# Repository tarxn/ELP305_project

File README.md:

# BIG BLACK co.
BIG BLACK Chargers & BIG BLACK Cables

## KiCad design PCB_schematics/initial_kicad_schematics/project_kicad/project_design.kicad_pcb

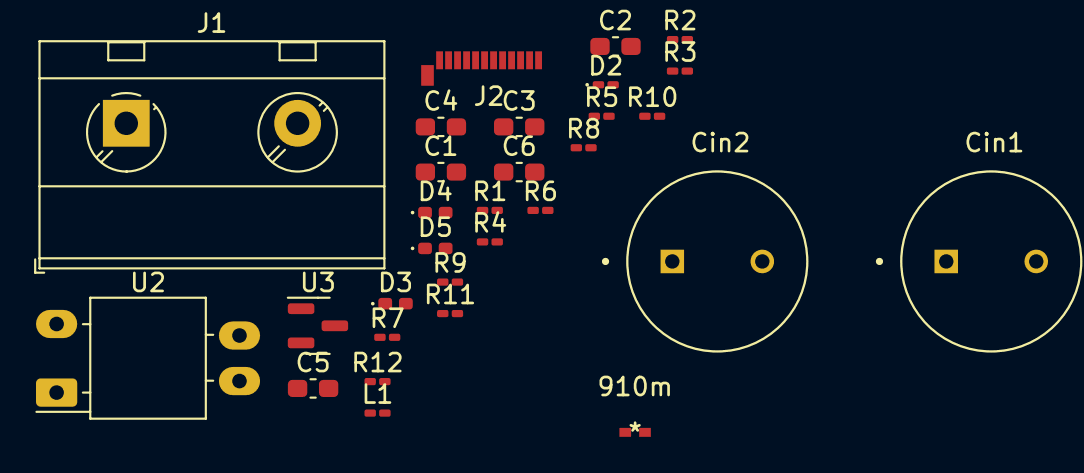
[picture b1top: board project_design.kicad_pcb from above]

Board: 2 copper layers, 30 parts (0 on the bottom side), 15 nets, no tracks yet.

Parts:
C1, C2: 22uF; C_0603_1608Metric_Pad1.08x0.95mm_HandSolder
C3: 4.7uF; C_0603_1608Metric_Pad1.08x0.95mm_HandSolder
C4: 100nF; C_0603_1608Metric_Pad1.08x0.95mm_HandSolder
C5: 882.393pF; C_0603_1608Metric_Pad1.08x0.95mm_HandSolder
C6: 1.2mF; C_0603_1608Metric_Pad1.08x0.95mm_HandSolder
Cin1, Cin2: 22uF; 400PK22MEFC12.5X20
D2: D_Zener; D_0201_0603Metric_Pad0.64x0.40mm_HandSolder
D3, D4, D5: D; D_0402_1005Metric_Pad0.77x0.64mm_HandSolder
J1: Screw_Terminal_01x02; TerminalBlock_MetzConnect_Type703_RT10N02HGLU_1x02_P9.52mm_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
J2: USB_C_Receptacle_PowerOnly_6P; USB_C_Plug_Molex_105444
L1: 470uH; L_0201_0603Metric_Pad0.64x0.40mm_HandSolder
R1: R; R_0201_0603Metric_Pad0.64x0.40mm_HandSolder
R2: 910m; R_0201_0603Metric_Pad0.64x0.40mm_HandSolder
R3: 2.21k; R_0201_0603Metric_Pad0.64x0.40mm_HandSolder
R4: 18.7k; R_0201_0603Metric_Pad0.64x0.40mm_HandSolder
R5: 205k; R_0201_0603Metric_Pad0.64x0.40mm_HandSolder
R6: 113k; R_0201_0603Metric_Pad0.64x0.40mm_HandSolder
R7: 34k; R_0201_0603Metric_Pad0.64x0.40mm_HandSolder
R8: 22; R_0201_0603Metric_Pad0.64x0.40mm_HandSolder
R9: 1k; R_0201_0603Metric_Pad0.64x0.40mm_HandSolder
R10: 1.07k; R_0201_0603Metric_Pad0.64x0.40mm_HandSolder
R11: 118k; R_0201_0603Metric_Pad0.64x0.40mm_HandSolder
R12: 39k; R_0201_0603Metric_Pad0.64x0.40mm_HandSolder
Rcs1: 910m; CRCW04021K07FKED
U2: NSL-32; Luna_NSL-32
U3: CJ432; SOT-23

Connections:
Earth: C1.2, C2.2, C3.1, C6.1, J2.A12 (GND), J2.B12 (GND), R2.1, R4.1, R7.1, R12.1, Rcs1.1, U3.3 (A)
unnamed: C3.2, D4.1 (K), U2.4 (R)
unnamed: C4.1, R4.2, R5.1
unnamed: C4.2, R5.2, U2.3 (R)
unnamed: C5.1, R9.1, U2.2 (K), U3.2 (K)
unnamed: C5.2, R11.1, R12.2, U3.1 (REF)
unnamed: C6.2, D5.1 (K), J2.A9 (VBUS), J2.B9 (VBUS), R10.2, R11.2
unnamed: D2.1 (K), D3.1 (K)
unnamed: D2.2 (A), L1.2
unnamed: D4.2 (A), R8.1
unnamed: J1.1, R1.1
unnamed: R2.2, R3.1, Rcs1.2
unnamed: R6.1, R7.2
unnamed: R6.2, R8.2
unnamed: R9.2, R10.1, U2.1 (A)

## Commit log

2023-02-17 adding existing files
2023-02-17 final ckt
2023-02-18 Create footprints
2023-02-18 added footprint parts 23-27
2023-02-18 Add files via upload
    part 11-14 of excel spreadsheet
2023-02-18 Add files via upload
    Rs1
    Part Number - CRCW0402113KFKED
2023-02-18 Rename DIOM5226X230N.kicad_mod to DIOM5226X230N_part23.kicad_mod
2023-02-18 Rename RESC2012X60N.kicad_mod to RESC2012X60N_part24.kicad_mod
2023-02-18 Rename RESC0603X26N.kicad_mod to RESC0603X26N_part25.kicad_mod
2023-02-18 Rename RESC1607X60N.kicad_mod to RESC1607X60N_part26.kicad_mod
2023-02-18 Rename RESC1005X40N.kicad_mod to RESC1005X40N_part27.kicad_mod
2023-02-18 designs
2023-02-19 WBDesign6
    I have added both the files that I got when I saved
2023-02-19 cad added
2023-02-20 merge
2023-02-20 clear up
2023-02-20 measure
2023-02-21 added pspice simulation and model files
2023-02-21 adoc
2023-02-27 added report file
2023-02-27 packaging
2023-02-27 box views
2023-03-02 final report
2023-03-02 final

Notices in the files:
parts and their libraries:
Copyright 2021 Accelerated Designs. All rights reserved.
